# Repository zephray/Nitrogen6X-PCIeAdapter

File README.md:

# Nitrogen6X-PCIeAdapter
PCIe adapter for Boundary Devices Nitrogen 6X

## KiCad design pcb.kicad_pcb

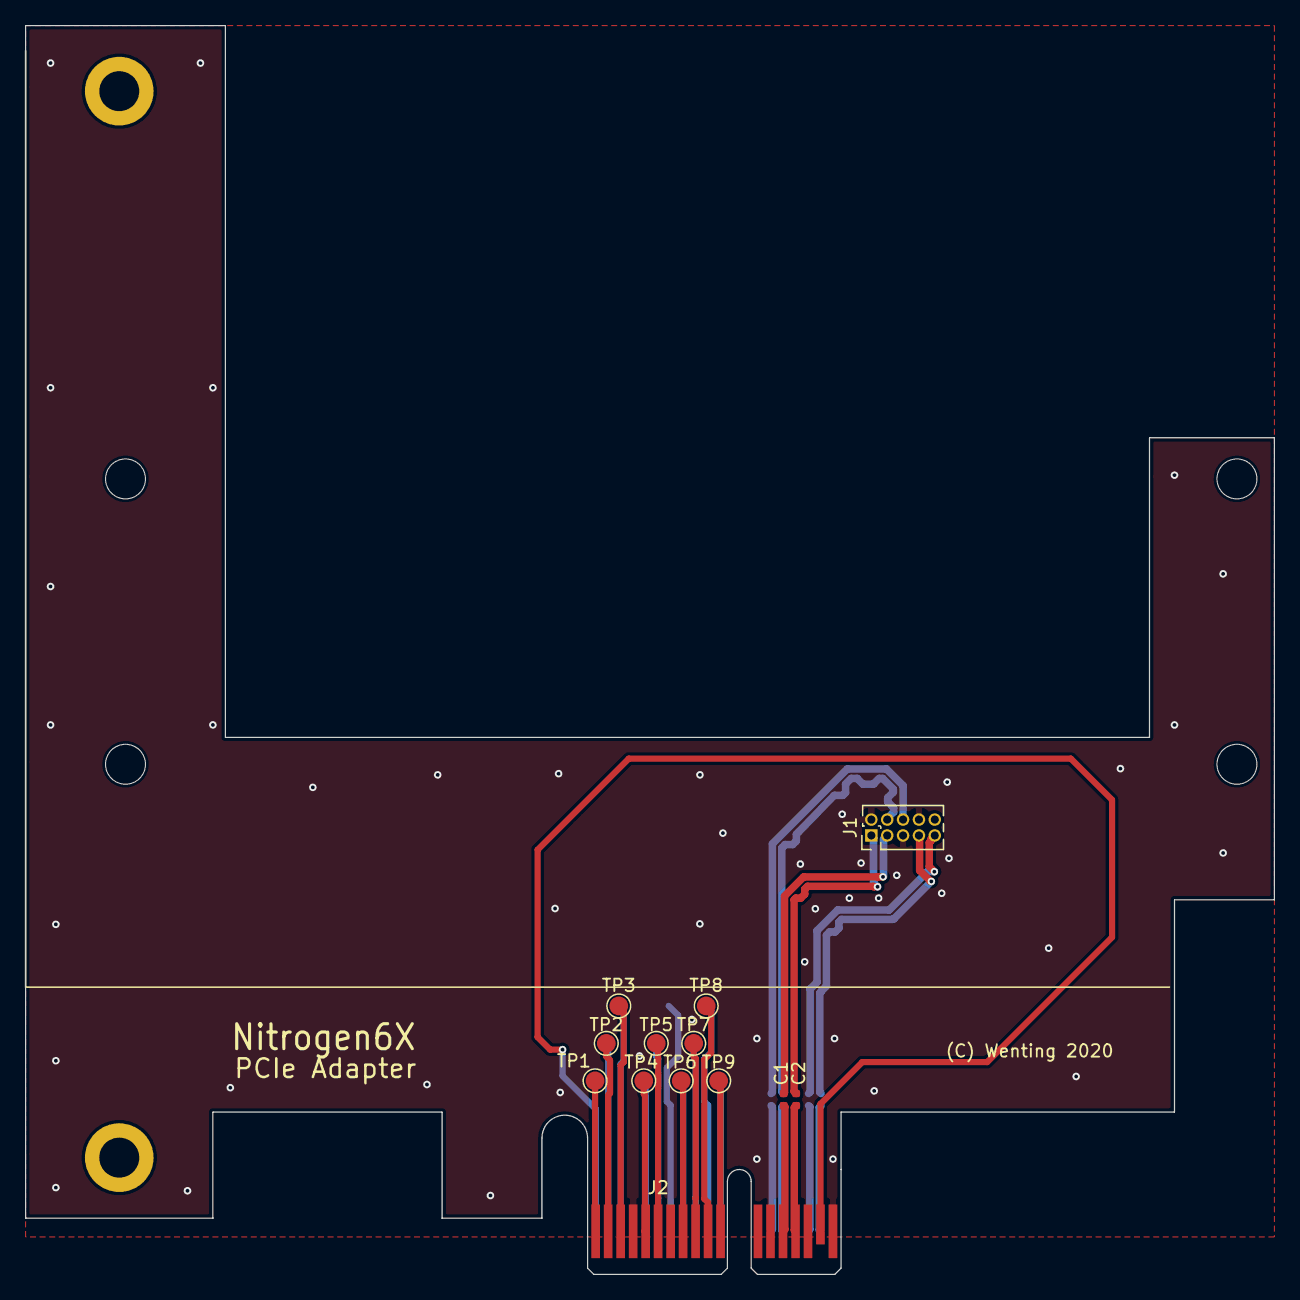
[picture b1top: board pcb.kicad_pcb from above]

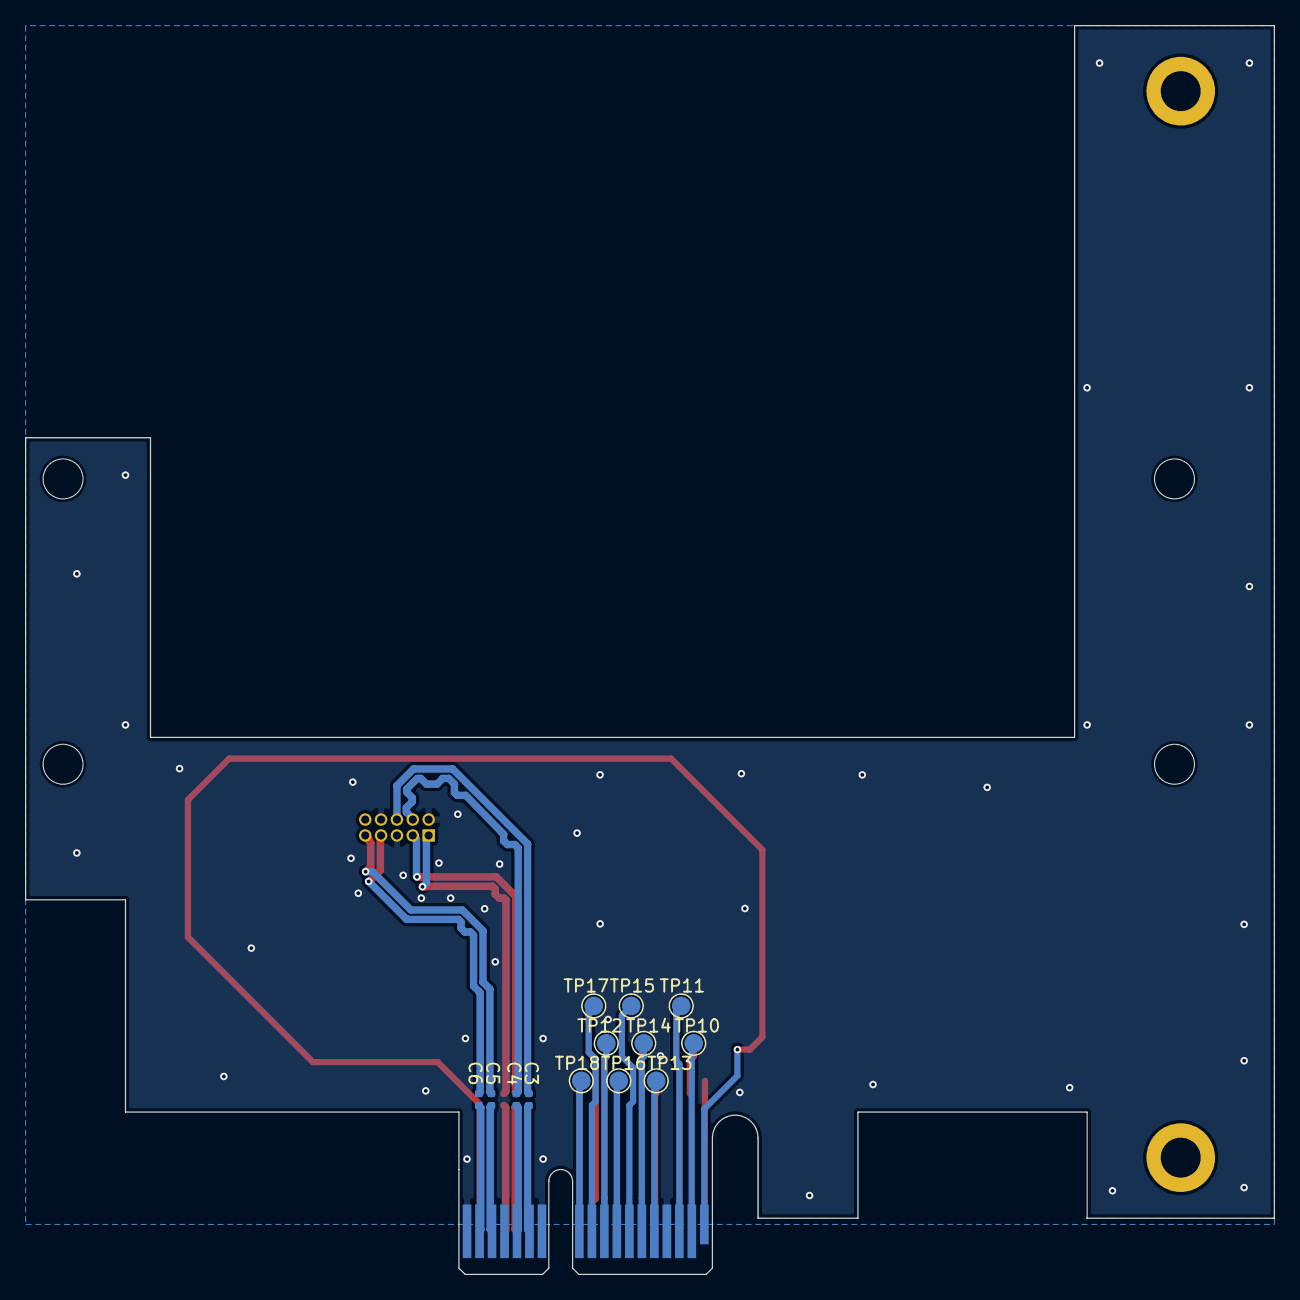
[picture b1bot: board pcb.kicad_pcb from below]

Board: 2 copper layers, 100.0 x 100.0 mm, 28 parts (13 on the bottom side), 32 nets.

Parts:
C1, C2, C3, C4, C5, C6: 10nF; C_0402_1005Metric
J1: Conn_02x05_Odd_Even; PinHeader_2x05_P1.27mm_Vertical
J2: Bus_PCIE_1x; BUS_PCIexpress_x1
MH1, MH3: MountingHole_3.2mm_M3_ISO14580_Pad
TP1, TP2, TP3, TP4, TP5, TP6, TP7, TP8, TP9, TP10, TP11, TP12, TP13, TP14, TP15, TP16, TP17, TP18: TestPoint; TestPoint_Pad_D1.5mm

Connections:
/PCIE_CLKN: C4.1, J1.4
/PCIE_CLKP: C3.1, J1.6
/PCIE_RXN0: C2.1, J1.1
/PCIE_RXP0: C1.1, J1.3
/PCIE_TXN0: C6.1, J1.7
/PCIE_TXP0: C5.1, J1.9
GND: J1.2, J1.5, J1.8, J2.A4, J2.A12, J2.A15, J2.A18, J2.B4, J2.B7, J2.B13, J2.B16, J2.B18
unnamed: C1.2, J2.B14
unnamed: C2.2, J2.B15
unnamed: C3.2, J2.A13
unnamed: C4.2, J2.A14
unnamed: C5.2, J2.A16
unnamed: C6.2, J2.A17
unnamed: J2.A1, J2.B17
unnamed: J2.A2, TP10.1
unnamed: J2.A3, TP11.1
unnamed: J2.A5, TP13.1
unnamed: J2.A6, TP14.1
unnamed: J2.A7, TP15.1
unnamed: J2.A8, TP16.1
unnamed: J2.A9, TP12.1
unnamed: J2.A10, TP17.1
unnamed: J2.A11, TP18.1
unnamed: J2.B1, TP1.1
unnamed: J2.B2, TP2.1
unnamed: J2.B3, TP3.1
unnamed: J2.B5, TP4.1
unnamed: J2.B6, TP5.1
unnamed: J2.B8, TP6.1
unnamed: J2.B9, TP7.1
unnamed: J2.B10, TP8.1
unnamed: J2.B11, TP9.1

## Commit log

2020-05-08 Initial revision
